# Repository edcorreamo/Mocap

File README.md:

## [ Esquemáticos ](https://github.com/edcorreamo/Mocap/tree/main/Esquematico)

En la presente sección va a encontrar el esquemático que se desarrollo para este proyecto ylas diferentes subsecciones que permiten conformar el circuito.

## [ Código ](https://github.com/JamesD004/MoCapUnal/tree/main/Imagenes)

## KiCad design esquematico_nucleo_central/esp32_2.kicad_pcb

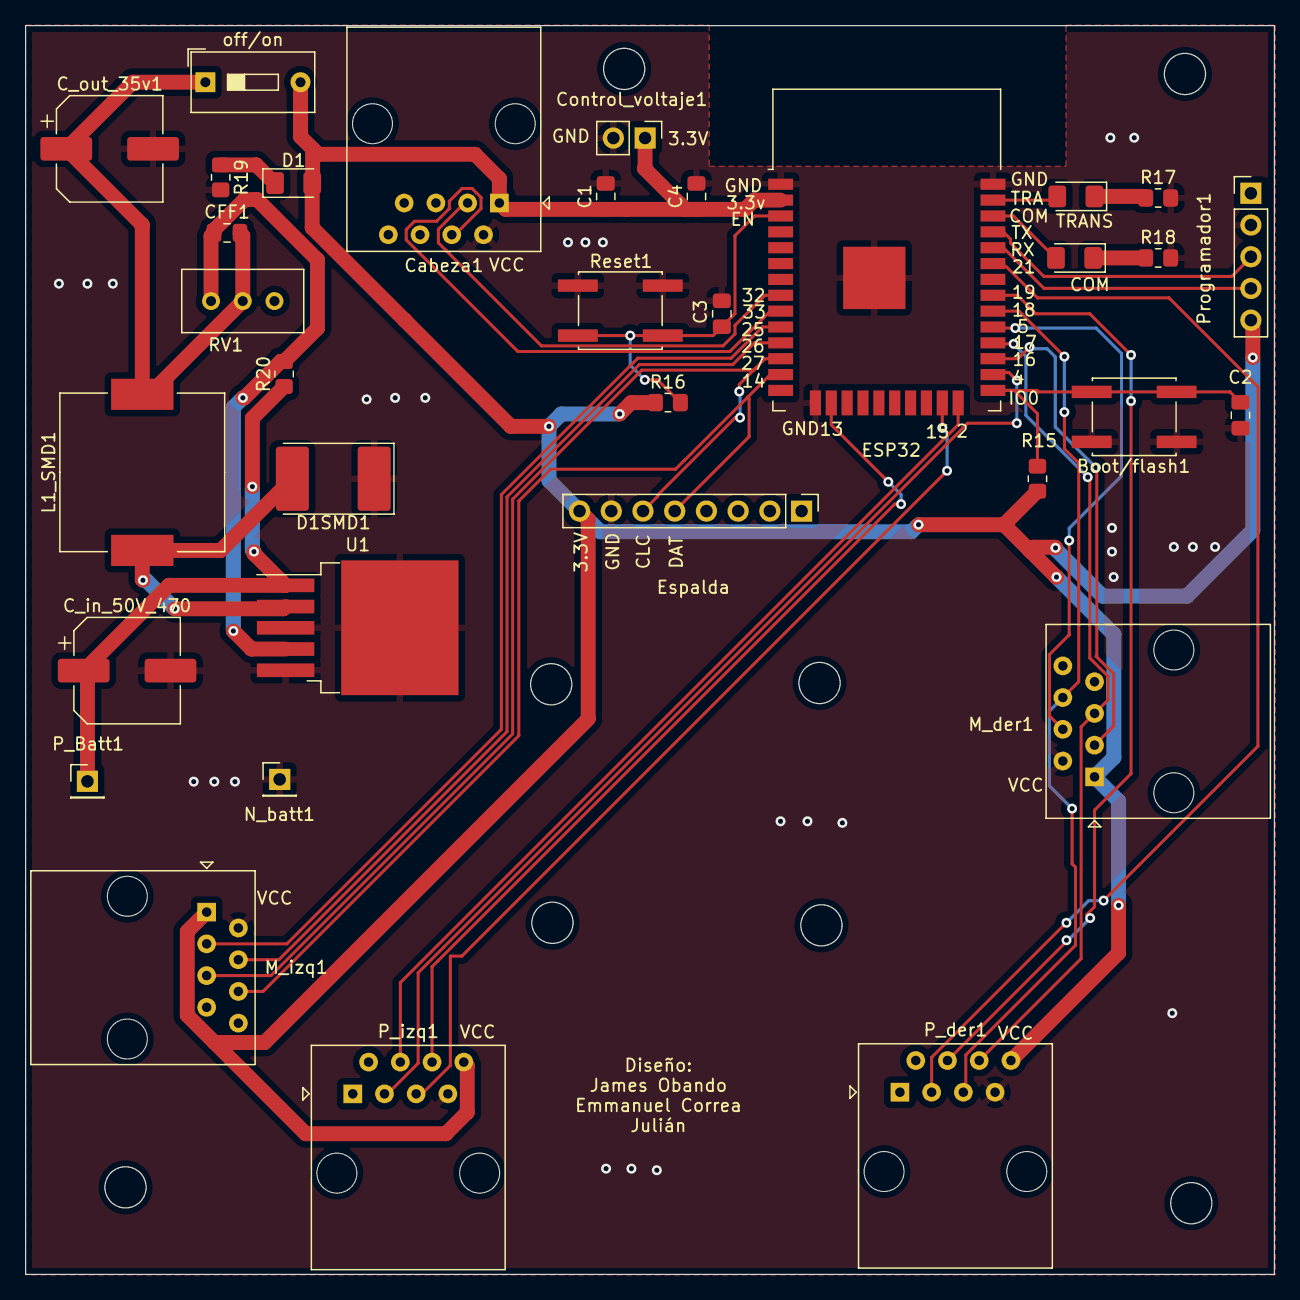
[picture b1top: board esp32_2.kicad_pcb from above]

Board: 2 copper layers, 100.0 x 100.0 mm, 34 parts (0 on the bottom side), 31 nets.

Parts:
Boot/flash1: SW_Push; SW_SPST_EVQQ2
C1: 10u; C_0805_2012Metric_Pad1.18x1.45mm_HandSolder
C2, C3: 1nF/50V; C_0805_2012Metric_Pad1.18x1.45mm_HandSolder
C4: 100u; C_0805_2012Metric_Pad1.18x1.45mm_HandSolder
CFF1: 1nf; C_0805_2012Metric_Pad1.18x1.45mm_HandSolder
COM: LED; LED_1206_3216Metric_Pad1.42x1.75mm_HandSolder
C_in_50V_470: 470u; CP_Elec_8x6.9
C_out_35v1: 220u; CP_Elec_8x6.9
Cabeza1: RJ45; RJ45_Amphenol_54602-x08_Horizontal
Control_voltaje1: Conn_01x02_Male; PinHeader_1x02_P2.54mm_Vertical
D1: LED; LED_1206_3216Metric_Pad1.42x1.75mm_HandSolder
D1SMD1: 1N5825; D_3220_8050Metric_Pad2.65x5.15mm_HandSolder
ESP32: ESP32-WROOM-32
Espalda: Conn_01x08_Male; PinHeader_1x08_P2.54mm_Vertical
L1_SMD1: 68u; L_Wuerth_HCM-1390
M_der1: RJ45; RJ45_Amphenol_54602-x08_Horizontal
M_izq1: RJ45; RJ45_Amphenol_54602-x08_Horizontal
N_batt1: Conn_01x01_Female; PinHeader_1x01_P2.54mm_Vertical
P_Batt1: Conn_01x01_Female; PinHeader_1x01_P2.54mm_Vertical
P_der1: RJ45; RJ45_Amphenol_54602-x08_Horizontal
P_izq1: RJ45; RJ45_Amphenol_54602-x08_Horizontal
Programador1: Programador; PinHeader_1x05_P2.54mm_Vertical
R15, R16, R17, R18, R19: 10k; R_0805_2012Metric_Pad1.20x1.40mm_HandSolder
R20: 1k; R_0805_2012Metric_Pad1.20x1.40mm_HandSolder
RV1: R_Potentiometer_Trim; Potentiometer_Bourns_3296W_Vertical
Reset1: SW_Push; SW_SPST_EVQQ2
TRANS: LED; LED_1206_3216Metric_Pad1.42x1.75mm_HandSolder
U1: LM2596S-5; TO-263-5_TabPin3
off/on: SW_DIP_x01; SW_DIP_SPSTx01_Slide_9.78x4.72mm_W7.62mm_P2.54mm

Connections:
+3V3: C1.1, C4.1, Cabeza1.1, Control_voltaje1.1, D1.2 (A), ESP32.2 (VDD), Espalda.8, M_der1.1, M_izq1.1, P_der1.8, P_izq1.8, Programador1.5, R15.1, R16.1, off/on.2
+5V: C_in_50V_470.1, P_Batt1.1, R20.1, U1.1 (VIN)
/CLC_1: Cabeza1.3, ESP32.8 (IO32)
/CLC_2: ESP32.10 (IO25), M_izq1.3
/CLC_3: ESP32.12 (IO27), Espalda.6, M_izq1.5
/CLC_4: ESP32.16 (IO13), P_izq1.6
/CLC_5: ESP32.24 (IO2), P_izq1.4
/CLC_6: ESP32.27 (IO16), M_der1.3
/CLC_7: ESP32.28 (IO17), M_der1.5, P_der1.6
/CLC_8: ESP32.31 (IO19), P_der1.4
/COMUNICACION: COM.2 (A), ESP32.36 (IO22)
/DATA_1: Cabeza1.4, ESP32.9 (IO33)
/DATA_2: ESP32.11 (IO26), M_izq1.4
/DATA_3: ESP32.13 (IO14), Espalda.5, M_izq1.6
/DATA_4: ESP32.23 (IO15), P_izq1.5
/DATA_5: ESP32.26 (IO4), P_izq1.3
/DATA_6: ESP32.29 (IO5), M_der1.4
/DATA_7: ESP32.30 (IO18), M_der1.6, P_der1.5
/DATA_8: ESP32.33 (IO21), P_der1.3
/EN: C3.2, ESP32.3 (EN), R16.2, Reset1.2
/IO0: Boot/flash1.2, C2.2, ESP32.25 (IO0), R15.2
/TRANSMISION: ESP32.37 (IO23), TRANS.2 (A)
GND: Boot/flash1.1, C1.2, C2.1, C3.1, C4.2, C_in_50V_470.2, C_out_35v1.2, Cabeza1.2, Control_voltaje1.2, D1SMD1.1 (K), ESP32.1 (GND), ESP32.15 (GND), ESP32.38 (GND), ESP32.39 (GND), Espalda.7, M_der1.2, M_izq1.2, N_batt1.1, P_der1.7, P_izq1.7, Programador1.2, R17.2, R18.2, R19.2, Reset1.1, U1.3 (GND), U1.5 (~ON/OFF)
unnamed: CFF1.1, R20.2, RV1.1, U1.4 (FB)
unnamed: CFF1.2, C_out_35v1.1, L1_SMD1.2, RV1.2, off/on.1
unnamed: D1.1 (K), R19.1
unnamed: D1SMD1.2 (A), L1_SMD1.1, U1.2 (OUT)
unnamed: COM.1 (K), R18.1
unnamed: R17.1, TRANS.1 (K)
unnamed: ESP32.34 (RXD0/IO3), Programador1.4
unnamed: ESP32.35 (TXD0/IO1), Programador1.3

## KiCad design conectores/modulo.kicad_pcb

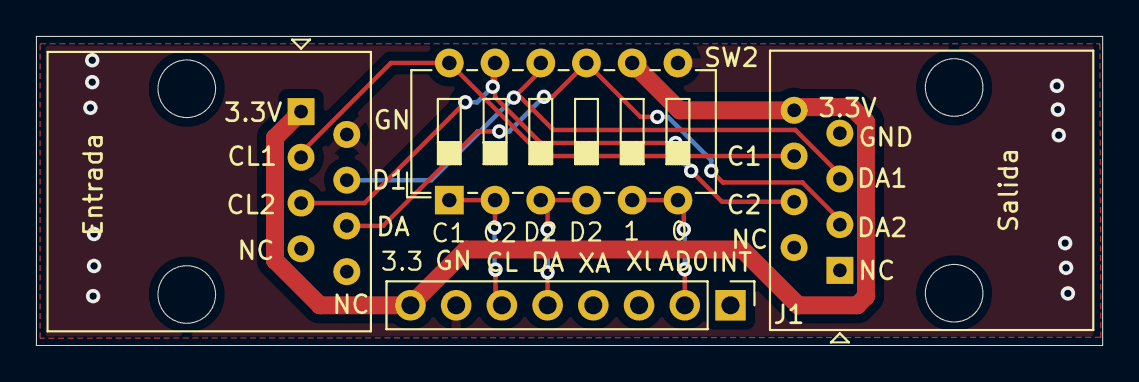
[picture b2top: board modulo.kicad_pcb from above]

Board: 2 copper layers, 59.2 x 17.2 mm, 4 parts (0 on the bottom side), 9 nets.

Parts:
Entrada: RJ45; RJ45_Amphenol_54602-x08_Horizontal
J1: Conn_01x08_Female; PinHeader_1x08_P2.54mm_Vertical
SW2: SW_DIP_x06; SW_DIP_SPSTx06_Slide_6.7x16.8mm_W7.62mm_P2.54mm_LowProfile
Salida: RJ45; RJ45_Amphenol_54602-x08_Horizontal

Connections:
+3V3: Entrada.1, J1.8, SW2.8, Salida.8
GND: Entrada.2, J1.7, SW2.7, Salida.7
unnamed: Entrada.3, SW2.12, Salida.6
unnamed: Entrada.4, SW2.10, Salida.5
unnamed: Entrada.5, SW2.11, Salida.4
unnamed: Entrada.6, SW2.9, Salida.3
unnamed: J1.2, SW2.5, SW2.6
unnamed: J1.5, SW2.3, SW2.4
unnamed: J1.6, SW2.1, SW2.2

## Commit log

2022-03-26 inicio a subir el material pendiente
2022-03-26 Create image
2022-05-08 Agregue la carpeta esquematico
2022-05-23 actualizar
2022-05-28 Cambié la ubicación de los archivos a la wiki
2022-06-06 listas de elementos
2022-07-05 Add files via upload
    pruebas_preliminares
2022-07-07 poster
2022-07-07 Create Datasheets
2022-07-07 Create File
2022-07-07 Create Prueba
